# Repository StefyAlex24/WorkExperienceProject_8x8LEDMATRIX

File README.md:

# WorkExperienceProject_8x8LEDMATRIX

Arduino Nano based 8x8 LED matrix board with MAX7219 Controller.
Refer to file: 8x8 LED Matrix.docx for project info.
Also includes Arduino Code files to get you started on your journey.

This project is intended as a work experience assignment for school children of age 14 and over.
The code for this project is based off other open source examples with only minor additions and modifications.

Forking of this project is encouraged.

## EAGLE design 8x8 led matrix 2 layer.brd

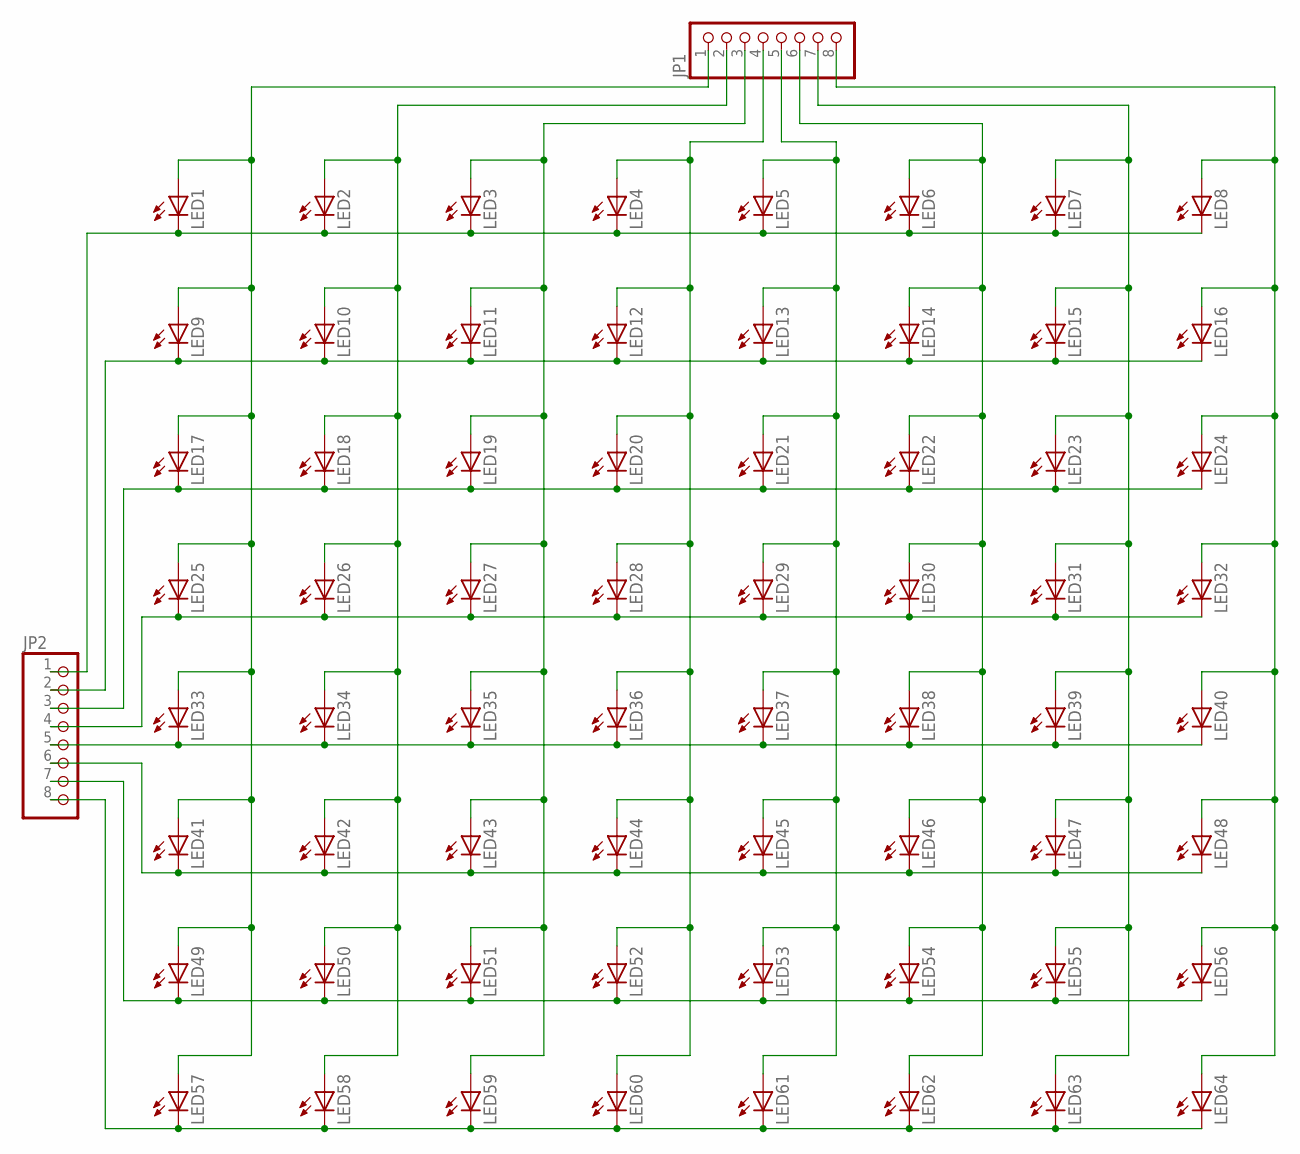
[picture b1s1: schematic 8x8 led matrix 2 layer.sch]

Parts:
JP1, JP2: PINHD-1X8; 1X08
LED1, LED2, LED3, LED4, LED5, LED6, LED7, LED8, LED9, LED10, LED11, LED12, LED13, LED14, LED15, LED16, LED17, LED18, LED19, LED20, LED21, LED22, LED23, LED24, LED25, LED26, LED27, LED28, LED29, LED30, LED31, LED32, LED33, LED34, LED35, LED36, LED37, LED38, LED39, LED40, LED41, LED42, LED43, LED44, LED45, LED46, LED47, LED48, LED49, LED50, LED51, LED52, LED53, LED54, LED55, LED56, LED57, LED58, LED59, LED60, LED61, LED62, LED63, LED64: LED5MM

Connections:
unnamed: JP1.4, LED4.A, LED12.A, LED20.A, LED28.A, LED36.A, LED44.A, LED52.A, LED60.A
unnamed: JP1.5, LED5.A, LED13.A, LED21.A, LED29.A, LED37.A, LED45.A, LED53.A, LED61.A
unnamed: JP1.1, LED1.A, LED9.A, LED17.A
unnamed: JP1.3, LED3.A, LED11.A, LED19.A, LED27.A, LED35.A, LED43.A, LED51.A, LED59.A
unnamed: JP1.6, LED6.A, LED14.A, LED22.A, LED30.A, LED38.A, LED46.A, LED54.A, LED62.A
unnamed: JP1.7, LED7.A, LED15.A, LED23.A, LED31.A, LED39.A, LED47.A, LED55.A, LED63.A
unnamed: JP2.1, LED1.K (C), LED2.K (C), LED3.K (C), LED4.K (C), LED5.K (C), LED6.K (C), LED7.K (C), LED8.K (C)
unnamed: JP2.2, LED9.K (C), LED10.K (C), LED11.K (C), LED12.K (C), LED13.K (C), LED14.K (C), LED15.K (C), LED16.K (C)
unnamed: JP2.3, LED17.K (C), LED18.K (C), LED19.K (C), LED20.K (C), LED21.K (C), LED22.K (C), LED23.K (C), LED24.K (C)
unnamed: LED25.A, LED33.A, LED41.A, LED49.A, LED57.A
unnamed: JP2.4, LED25.K (C), LED26.K (C), LED27.K (C), LED28.K (C), LED29.K (C), LED30.K (C), LED31.K (C), LED32.K (C)
unnamed: JP2.5, LED33.K (C), LED34.K (C), LED35.K (C), LED36.K (C), LED37.K (C), LED38.K (C), LED39.K (C), LED40.K (C)
unnamed: JP2.6, LED41.K (C), LED42.K (C), LED43.K (C), LED44.K (C), LED45.K (C), LED46.K (C), LED47.K (C), LED48.K (C)
unnamed: JP1.8, LED8.A, LED16.A, LED24.A, LED32.A, LED40.A, LED48.A, LED56.A, LED64.A
unnamed: JP2.7, LED49.K (C), LED50.K (C), LED51.K (C), LED52.K (C), LED53.K (C), LED54.K (C), LED55.K (C), LED56.K (C)
unnamed: JP1.2, LED2.A, LED10.A, LED18.A, LED26.A, LED34.A, LED42.A, LED50.A, LED58.A
unnamed: JP2.8, LED57.K (C), LED58.K (C), LED59.K (C), LED60.K (C), LED61.K (C), LED62.K (C), LED63.K (C), LED64.K (C)

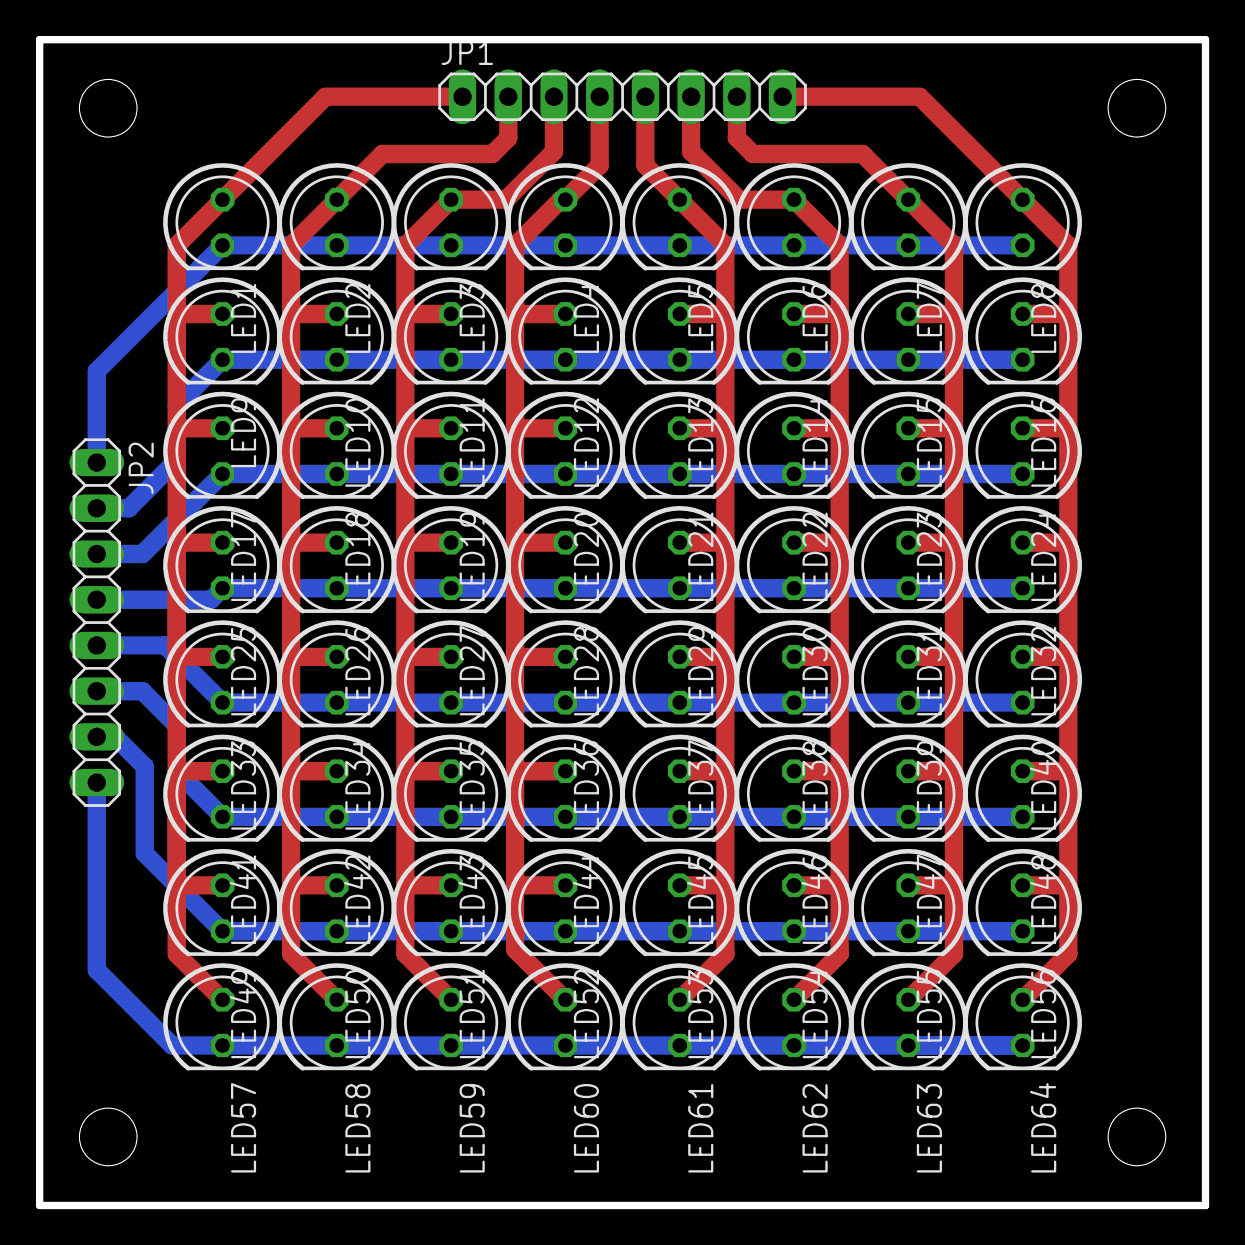
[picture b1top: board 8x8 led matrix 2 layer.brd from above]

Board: 2 copper layers, 64.8 x 64.8 mm, 66 parts (0 on the bottom side), 17 nets.

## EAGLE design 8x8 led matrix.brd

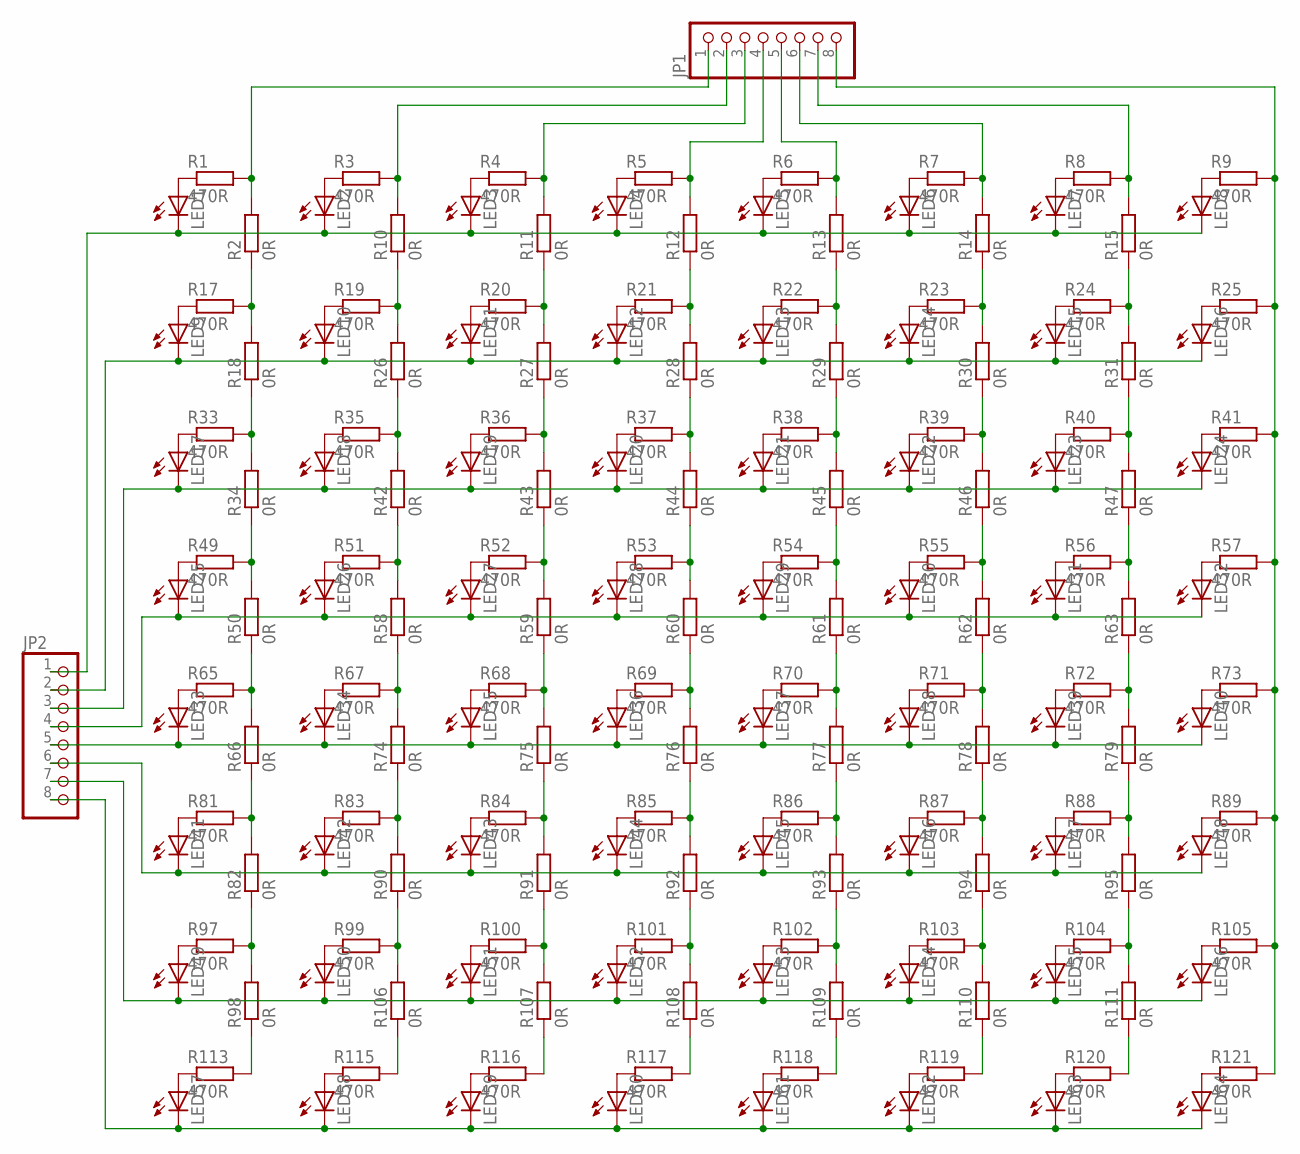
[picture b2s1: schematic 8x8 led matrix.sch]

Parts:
JP1, JP2: PINHD-1X8; 1X08
LED1, LED2, LED3, LED4, LED5, LED6, LED7, LED8, LED9, LED10, LED11, LED12, LED13, LED14, LED15, LED16, LED17, LED18, LED19, LED20, LED21, LED22, LED23, LED24, LED25, LED26, LED27, LED28, LED29, LED30, LED31, LED32, LED33, LED34, LED35, LED36, LED37, LED38, LED39, LED40, LED41, LED42, LED43, LED44, LED45, LED46, LED47, LED48, LED49, LED50, LED51, LED52, LED53, LED54, LED55, LED56, LED57, LED58, LED59, LED60, LED61, LED62, LED63, LED64: LED5MM
R1, R3, R4, R5, R6, R7, R8, R9, R17, R19, R20, R21, R22, R23, R24, R25, R33, R35, R36, R37, R38, R39, R40, R41, R49, R51, R52, R53, R54, R55, R56, R57, R65, R67, R68, R69, R70, R71, R72, R73, R81, R83, R84, R85, R86, R87, R88, R89, R97, R99, R100, R101, R102, R103, R104, R105, R113, R115, R116, R117, R118, R119, R120, R121: 470R; R0603
R2, R10, R11, R12, R13, R14, R15, R18, R26, R27, R28, R29, R30, R31, R34, R42, R43, R44, R45, R46, R47, R50, R58, R59, R60, R61, R62, R63, R66, R74, R75, R76, R77, R78, R79, R82, R90, R91, R92, R93, R94, R95, R98, R106, R107, R108, R109, R110, R111: 0R; R1206

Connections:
unnamed: LED1.A, R1.1
unnamed: LED2.A, R3.1
unnamed: LED3.A, R4.1
unnamed: LED4.A, R5.1
unnamed: LED5.A, R6.1
unnamed: LED6.A, R7.1
unnamed: LED7.A, R8.1
unnamed: LED8.A, R9.1
unnamed: JP1.4, R5.2, R12.2
unnamed: JP1.5, R6.2, R13.2
unnamed: JP1.1, R1.2, R2.2
unnamed: JP1.2, R3.2, R10.2
unnamed: JP1.3, R4.2, R11.2
unnamed: JP1.6, R7.2, R14.2
unnamed: JP1.7, R8.2, R15.2
unnamed: JP2.1, LED1.K (C), LED2.K (C), LED3.K (C), LED4.K (C), LED5.K (C), LED6.K (C), LED7.K (C), LED8.K (C)
unnamed: LED9.A, R17.1
unnamed: LED10.A, R19.1
unnamed: LED11.A, R20.1
unnamed: LED12.A, R21.1
unnamed: LED13.A, R22.1
unnamed: LED14.A, R23.1
unnamed: LED15.A, R24.1
unnamed: LED16.A, R25.1
unnamed: R2.1, R17.2, R18.2
unnamed: R10.1, R19.2, R26.2
unnamed: R11.1, R20.2, R27.2
unnamed: R12.1, R21.2, R28.2
unnamed: R13.1, R22.2, R29.2
unnamed: R14.1, R23.2, R30.2
unnamed: R15.1, R24.2, R31.2
unnamed: JP2.2, LED9.K (C), LED10.K (C), LED11.K (C), LED12.K (C), LED13.K (C), LED14.K (C), LED15.K (C), LED16.K (C)
unnamed: LED17.A, R33.1
unnamed: LED18.A, R35.1
unnamed: LED19.A, R36.1
unnamed: LED20.A, R37.1
unnamed: LED21.A, R38.1
unnamed: LED22.A, R39.1
unnamed: LED23.A, R40.1
unnamed: LED24.A, R41.1
unnamed: R18.1, R33.2, R34.2
unnamed: R26.1, R35.2, R42.2
unnamed: R27.1, R36.2, R43.2
unnamed: R28.1, R37.2, R44.2
unnamed: R29.1, R38.2, R45.2
unnamed: R30.1, R39.2, R46.2
unnamed: R31.1, R40.2, R47.2
unnamed: JP2.3, LED17.K (C), LED18.K (C), LED19.K (C), LED20.K (C), LED21.K (C), LED22.K (C), LED23.K (C), LED24.K (C)
unnamed: LED25.A, R49.1
unnamed: LED26.A, R51.1
unnamed: LED27.A, R52.1
unnamed: LED28.A, R53.1
unnamed: LED29.A, R54.1
unnamed: LED30.A, R55.1
unnamed: LED31.A, R56.1
unnamed: LED32.A, R57.1
unnamed: R34.1, R49.2, R50.2
unnamed: R42.1, R51.2, R58.2
unnamed: R43.1, R52.2, R59.2
unnamed: R44.1, R53.2, R60.2
unnamed: R45.1, R54.2, R61.2
unnamed: R46.1, R55.2, R62.2
unnamed: R47.1, R56.2, R63.2
unnamed: JP2.4, LED25.K (C), LED26.K (C), LED27.K (C), LED28.K (C), LED29.K (C), LED30.K (C), LED31.K (C), LED32.K (C)
unnamed: LED33.A, R65.1
unnamed: LED34.A, R67.1
unnamed: LED35.A, R68.1
unnamed: LED36.A, R69.1
unnamed: LED37.A, R70.1
unnamed: LED38.A, R71.1
unnamed: LED39.A, R72.1
unnamed: LED40.A, R73.1
unnamed: R50.1, R65.2, R66.2
unnamed: R58.1, R67.2, R74.2
unnamed: R59.1, R68.2, R75.2
unnamed: R60.1, R69.2, R76.2
unnamed: R61.1, R70.2, R77.2
unnamed: R62.1, R71.2, R78.2
unnamed: R63.1, R72.2, R79.2
unnamed: JP2.5, LED33.K (C), LED34.K (C), LED35.K (C), LED36.K (C), LED37.K (C), LED38.K (C), LED39.K (C), LED40.K (C)
unnamed: LED41.A, R81.1
unnamed: LED42.A, R83.1
unnamed: LED43.A, R84.1
unnamed: LED44.A, R85.1
unnamed: LED45.A, R86.1
unnamed: LED46.A, R87.1
unnamed: LED47.A, R88.1
unnamed: LED48.A, R89.1
unnamed: R66.1, R81.2, R82.2
unnamed: R74.1, R83.2, R90.2
unnamed: R75.1, R84.2, R91.2
unnamed: R76.1, R85.2, R92.2
unnamed: R77.1, R86.2, R93.2
unnamed: R78.1, R87.2, R94.2
unnamed: R79.1, R88.2, R95.2
unnamed: JP2.6, LED41.K (C), LED42.K (C), LED43.K (C), LED44.K (C), LED45.K (C), LED46.K (C), LED47.K (C), LED48.K (C)
unnamed: LED49.A, R97.1
unnamed: LED50.A, R99.1
unnamed: LED51.A, R100.1
unnamed: LED52.A, R101.1
unnamed: LED53.A, R102.1
unnamed: LED54.A, R103.1
unnamed: LED55.A, R104.1
unnamed: LED56.A, R105.1
unnamed: R82.1, R97.2, R98.2
unnamed: R90.1, R99.2, R106.2
unnamed: R91.1, R100.2, R107.2
unnamed: R92.1, R101.2, R108.2
unnamed: R93.1, R102.2, R109.2
unnamed: R94.1, R103.2, R110.2
unnamed: R95.1, R104.2, R111.2
unnamed: JP1.8, R9.2, R25.2, R41.2, R57.2, R73.2, R89.2, R105.2, R121.2
unnamed: JP2.7, LED49.K (C), LED50.K (C), LED51.K (C), LED52.K (C), LED53.K (C), LED54.K (C), LED55.K (C), LED56.K (C)
unnamed: LED57.A, R113.1
unnamed: LED58.A, R115.1
unnamed: LED59.A, R116.1
unnamed: LED60.A, R117.1
unnamed: LED61.A, R118.1
unnamed: LED62.A, R119.1
unnamed: LED63.A, R120.1
unnamed: LED64.A, R121.1
unnamed: R98.1, R113.2
unnamed: R106.1, R115.2
unnamed: R107.1, R116.2
unnamed: R108.1, R117.2
unnamed: R109.1, R118.2
unnamed: R110.1, R119.2
unnamed: R111.1, R120.2
unnamed: JP2.8, LED57.K (C), LED58.K (C), LED59.K (C), LED60.K (C), LED61.K (C), LED62.K (C), LED63.K (C), LED64.K (C)

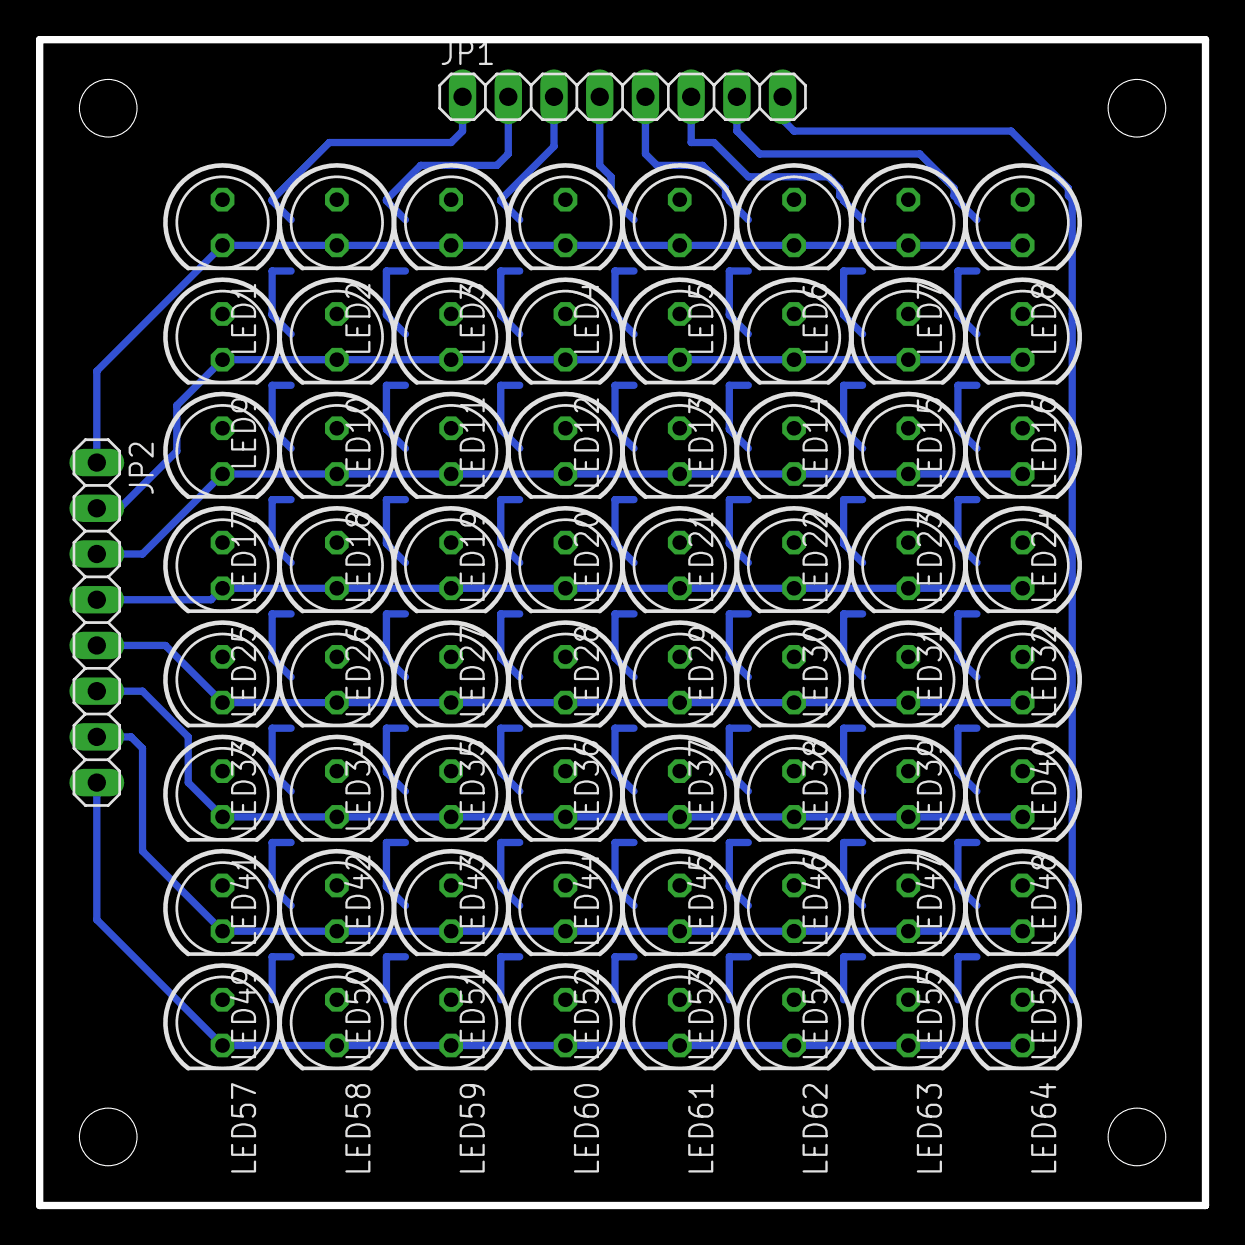
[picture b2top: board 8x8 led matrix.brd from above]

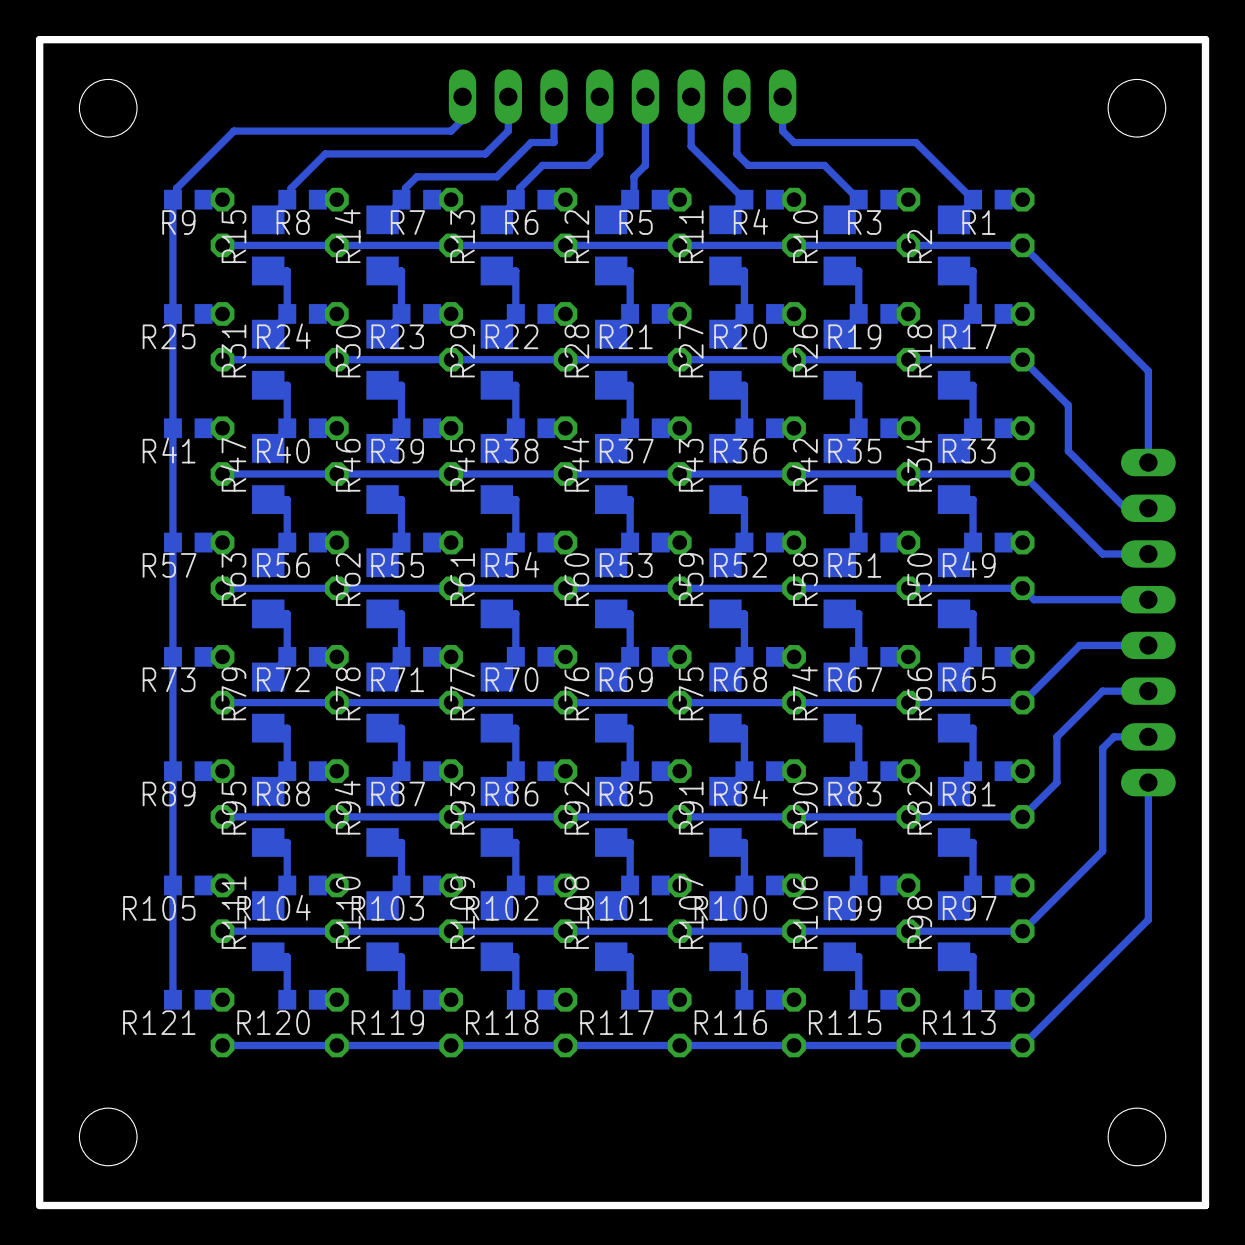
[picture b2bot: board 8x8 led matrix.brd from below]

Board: 2 copper layers, 64.8 x 64.8 mm, 179 parts (113 on the bottom side), 129 nets.

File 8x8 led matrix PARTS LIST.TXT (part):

Partlist

Exported from 8x8 led matrix.brd at 16/08/2016 16:32

EAGLE Version 7.5.0 Copyright (c) 1988-2015 CadSoft

Assembly variant: 

Part     Value          Package  Library  Position (mm)         Orientation

JP1                     1X08     pinhead  (46.355 73.025)       R0
JP2                     1X08     pinhead  (17.145 43.815)       R270
LED1                    LED5MM   led      (24.13 66.04)         R270
LED2                    LED5MM   led      (30.48 66.04)         R270
LED3                    LED5MM   led      (36.83 66.04)         R270
LED4                    LED5MM   led      (43.18 66.04)         R270
LED5                    LED5MM   led      (49.53 66.04)         R270
LED6                    LED5MM   led      (55.88 66.04)         R270
LED7                    LED5MM   led      (62.23 66.04)         R270
LED8                    LED5MM   led      (68.58 66.04)         R270
LED9                    LED5MM   led      (24.13 59.69)         R270
LED10                   LED5MM   led      (30.48 59.69)         R270
LED11                   LED5MM   led      (36.83 59.69)         R270
LED12                   LED5MM   led      (43.18 59.69)         R270
LED13                   LED5MM   led      (49.53 59.69)         R270
LED14                   LED5MM   led      (55.88 59.69)         R270
LED15                   LED5MM   led      (62.23 59.69)         R270
LED16                   LED5MM   led      (68.58 59.69)         R270
LED17                   LED5MM   led      (24.13 53.34)         R270
LED18                   LED5MM   led      (30.48 53.34)         R270
LED19                   LED5MM   led      (36.83 53.34)         R270
LED20                   LED5MM   led      (43.18 53.34)         R270
LED21                   LED5MM   led      (49.53 53.34)         R270
LED22                   LED5MM   led      (55.88 53.34)         R270
LED23                   LED5MM   led      (62.23 53.34)         R270
LED24                   LED5MM   led      (68.58 53.34)         R270
LED25                   LED5MM   led      (24.13 46.99)         R270
LED26                   LED5MM   led      (30.48 46.99)         R270
LED27                   LED5MM   led      (36.83 46.99)         R270
LED28                   LED5MM   led      (43.18 46.99)         R270
LED29                   LED5MM   led      (49.53 46.99)         R270
LED30                   LED5MM   led      (55.88 46.99)         R270
LED31                   LED5MM   led      (62.23 46.99)         R270
LED32                   LED5MM   led      (68.58 46.99)         R270
LED33                   LED5MM   led      (24.13 40.64)         R270
LED34                   LED5MM   led      (30.48 40.64)         R270
LED35                   LED5MM   led      (36.83 40.64)         R270
LED36                   LED5MM   led      (43.18 40.64)         R270
LED37                   LED5MM   led      (49.53 40.64)         R270
LED38                   LED5MM   led      (55.88 40.64)         R270
LED39                   LED5MM   led      (62.23 40.64)         R270
LED40                   LED5MM   led      (68.58 40.64)         R270
LED41                   LED5MM   led      (24.13 34.29)         R270
LED42                   LED5MM   led      (30.48 34.29)         R270
LED43                   LED5MM   led      (36.83 34.29)         R270
LED44                   LED5MM   led      (43.18 34.29)         R270
LED45                   LED5MM   led      (49.53 34.29)         R270
LED46                   LED5MM   led      (55.88 34.29)         R270
LED47                   LED5MM   led      (62.23 34.29)         R270
LED48                   LED5MM   led      (68.58 34.29)         R270
LED49                   LED5MM   led      (24.13 27.94)         R270
LED50                   LED5MM   led      (30.48 27.94)         R270
LED51                   LED5MM   led      (36.83 27.94)         R270
LED52                   LED5MM   led      (43.18 27.94)         R270
LED53                   LED5MM   led      (49.53 27.94)         R270
LED54                   LED5MM   led      (55.88 27.94)         R270
LED55                   LED5MM   led      (62.23 27.94)         R270
LED56                   LED5MM   led      (68.58 27.94)         R270
LED57                   LED5MM   led      (24.13 21.59)         R270
LED58                   LED5MM   led      (30.48 21.59)         R270
LED59                   LED5MM   led      (36.83 21.59)         R270
LED60                   LED5MM   led      (43.18 21.59)         R270
LED61                   LED5MM   led      (49.53 21.59)         R270
LED62                   LED5MM   led      (55.88 21.59)         R270
LED63                   LED5MM   led      (62.23 21.59)         R270
LED64                   LED5MM   led      (68.58 21.59)         R270
R1       470R           R0603    resistor (26.035 67.31)        MR180
R2       0R             R1206    resistor (27.94 64.77)         MR90
R3       470R           R0603    resistor (32.385 67.31)        MR180
R4       470R           R0603    resistor (38.735 67.31)        MR180
R5       470R           R0603    resistor (45.085 67.31)        MR180
R6       470R           R0603    resistor (51.435 67.31)        MR180
R7       470R           R0603    resistor (57.785 67.31)        MR180
R8       470R           R0603    resistor (64.135 67.31)        MR180
R9       470R           R0603    resistor (70.485 67.31)        MR180
R10      0R             R1206    resistor (34.29 64.77)         MR90
R11      0R             R1206    resistor (40.64 64.77)         MR90
R12      0R             R1206    resistor (46.99 64.77)         MR90
R13      0R             R1206    resistor (53.34 64.77)         MR90
R14      0R             R1206    resistor (59.69 64.77)         MR90
R15      0R             R1206    resistor (66.04 64.77)         MR90
R17      470R           R0603    resistor (26.035 60.96)        MR180
R18      0R             R1206    resistor (27.94 58.42)         MR90
R19      470R           R0603    resistor (32.385 60.96)        MR180
R20      470R           R0603    resistor (38.735 60.96)        MR180
R21      470R           R0603    resistor (45.085 60.96)        MR180
R22      470R           R0603    resistor (51.435 60.96)        MR180
R23      470R           R0603    resistor (57.785 60.96)        MR180
R24      470R           R0603    resistor (64.135 60.96)        MR180
R25      470R           R0603    resistor (70.485 60.96)        MR180
R26      0R             R1206    resistor (34.29 58.42)         MR90
R27      0R             R1206    resistor (40.64 58.42)         MR90
R28      0R             R1206    resistor (46.99 58.42)         MR90
R29      0R             R1206    resistor (53.34 58.42)         MR90
R30      0R             R1206    resistor (59.69 58.42)         MR90
R31      0R             R1206    resistor (66.04 58.42)         MR90
R33      470R           R0603    resistor (26.035 54.61)        MR180
R34      0R             R1206    resistor (27.94 52.07)         MR90
R35      470R           R0603    resistor (32.385 54.61)        MR180
R36      470R           R0603    resistor (38.735 54.61)        MR180
R37      470R           R0603    resistor (45.085 54.61)        MR180
R38      470R           R0603    resistor (51.435 54.61)        MR180
R39      470R           R0603    resistor (57.785 54.61)        MR180
R40      470R           R0603    resistor (64.135 54.61)        MR180
R41      470R           R0603    resistor (70.485 54.61)        MR180
R42      0R             R1206    resistor (34.29 52.07)         MR90
R43      0R             R1206    resistor (40.64 52.07)         MR90
R44      0R             R1206    resistor (46.99 52.07)         MR90
R45      0R             R1206    resistor (53.34 52.07)         MR90
R46      0R             R1206    resistor (59.69 52.07)         MR90
R47      0R             R1206    resistor (66.04 52.07)         MR90
R49      470R           R0603    resistor (26.035 48.26)        MR180
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
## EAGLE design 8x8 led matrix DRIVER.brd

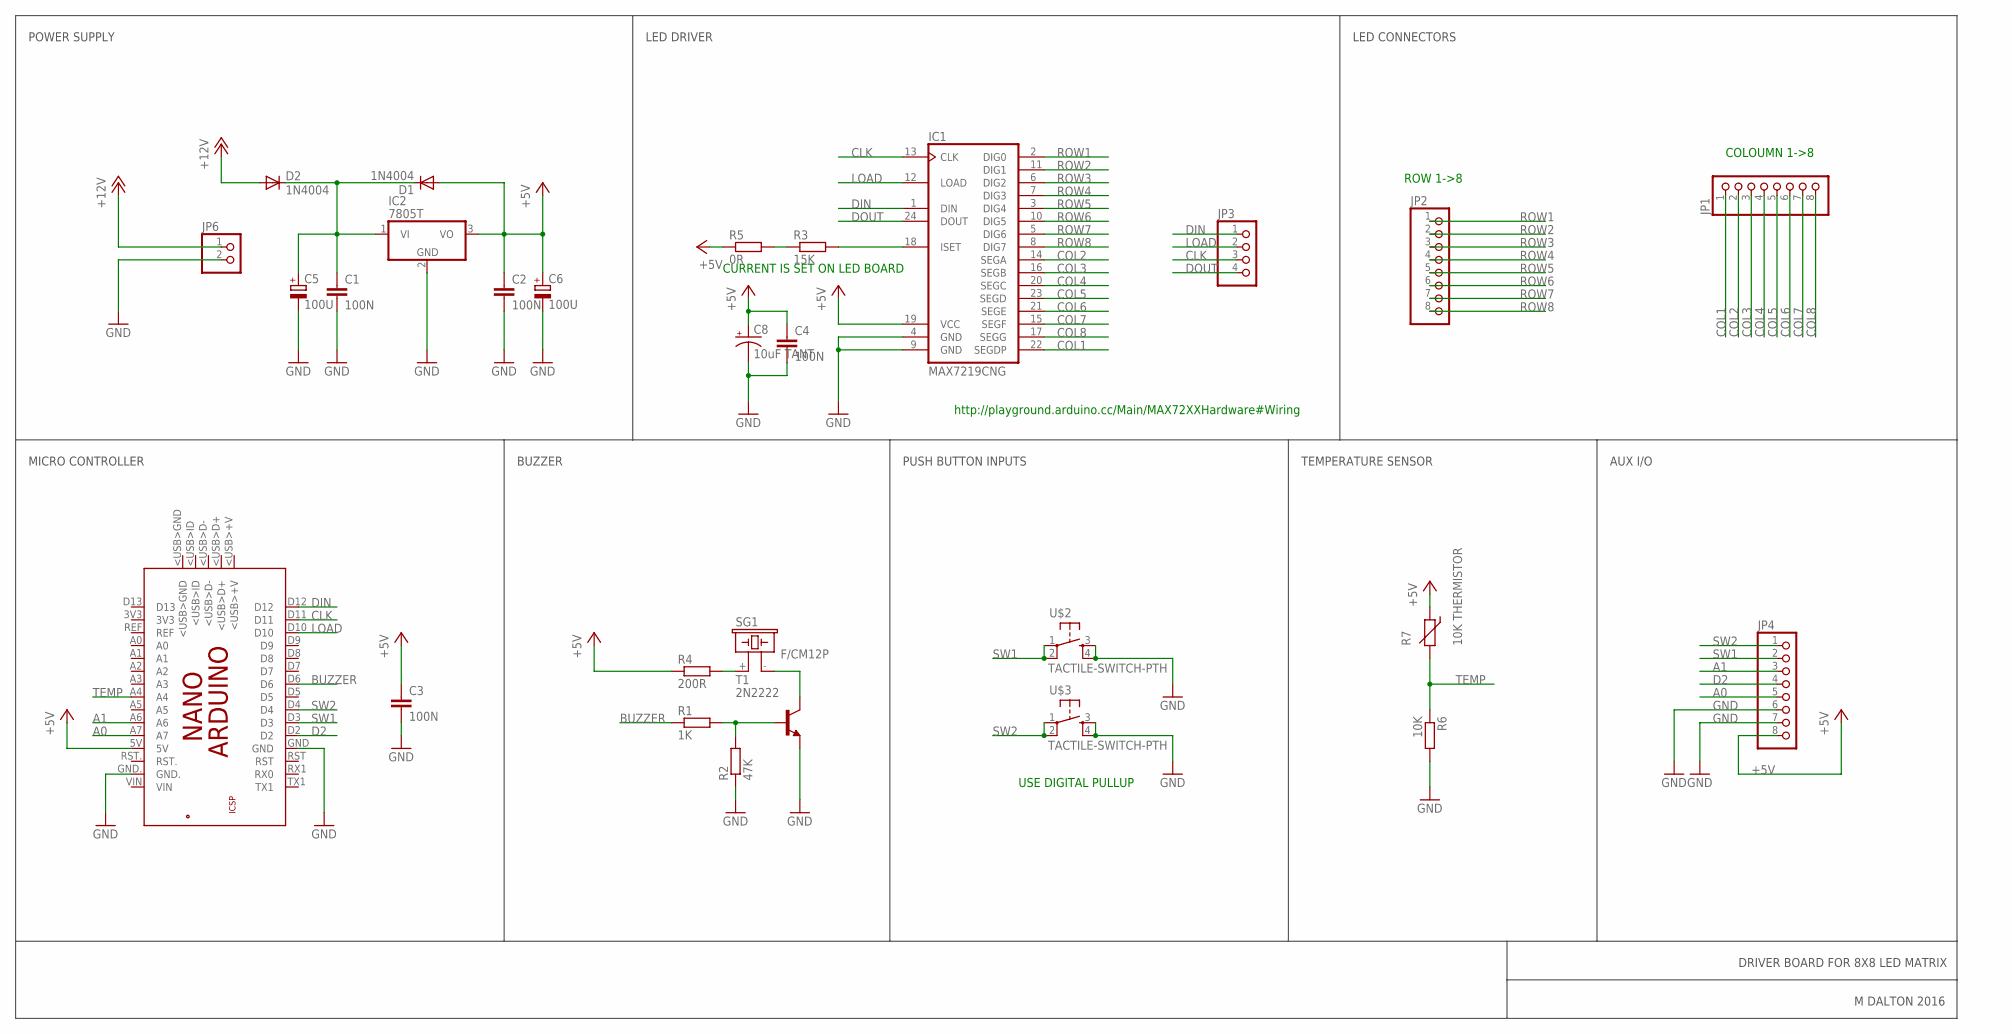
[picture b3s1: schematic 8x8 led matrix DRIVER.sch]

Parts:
C1, C2, C3, C4: 100N; C1206K
C5, C6: 100U; E5-10,5
C8: 10uF TANT; EIA3216
D1, D2: 1N4004; DO41-10
IC1: MAX7219CNG; DIL24-3
IC2: 7805T; TO220H
JP1, JP2, JP4: PINHD-1X8; 1X08
JP3: PINHD-1X4; 1X04
JP6: PINHD-1X2; 1X02
PCB1: ARDUINO_NANO
R1: 1K; M1206
R2: 47K; M1206
R3: 15K; M0805
R4: 200R; M1206
R5: 0R; M0805
R6: 10K; M1206
R7: 10K THERMISTOR; R-7,5
SG1: F/CM12P
T1: 2N2222; TO92-EBC-OVAL
U$2, U$3: TACTILE-SWITCH-PTH; TAC-SWITCH-PTH

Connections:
+5V: C2.1, C3.1, C4.1, C6.+, C8.A (+), D1.A, IC1.19 (VCC), IC2.3 (VO), JP4.8, PCB1.5V, R4.1, R5.1, R7.1
+12V: D2.A, JP6.1
A0: JP4.5, PCB1.A7
A1: JP4.3, PCB1.A6
BUZZER: PCB1.D6, R1.1
CLK: IC1.13 (CLK), JP3.3, PCB1.D11
COL1: IC1.22 (SEGDP), JP1.1
COL2: IC1.14 (SEGA), JP1.2
COL3: IC1.16 (SEGB), JP1.3
COL4: IC1.20 (SEGC), JP1.4
COL5: IC1.23 (SEGD), JP1.5
COL6: IC1.21 (SEGE), JP1.6
COL7: IC1.15 (SEGF), JP1.7
COL8: IC1.17 (SEGG), JP1.8
D2: JP4.4, PCB1.D2
DIN: IC1.1 (DIN), JP3.1, PCB1.D12
DOUT: IC1.24 (DOUT), JP3.4
GND: C1.2, C2.2, C3.2, C4.2, C5.-, C6.-, C8.C (-), IC1.4 (GND), IC1.9 (GND), IC2.2 (GND), JP4.6, JP4.7, JP6.2, PCB1.GND, PCB1.GND., R2.1, R6.2, T1.E, U$2.3, U$2.4, U$3.3, U$3.4
LOAD: IC1.12 (LOAD), JP3.2, PCB1.D10
unnamed: R3.1, R5.2
unnamed: C1.1, C5.+, D1.C, D2.C, IC2.1 (VI)
unnamed: IC1.18 (ISET), R3.2
unnamed: R1.2, R2.2, T1.B
unnamed: SG1.- (2), T1.C
unnamed: R4.2, SG1.+ (1)
ROW1: IC1.2 (DIG0), JP2.1
ROW2: IC1.11 (DIG1), JP2.2
ROW3: IC1.6 (DIG2), JP2.3
ROW4: IC1.7 (DIG3), JP2.4
ROW5: IC1.3 (DIG4), JP2.5
ROW6: IC1.10 (DIG5), JP2.6
ROW7: IC1.5 (DIG6), JP2.7
ROW8: IC1.8 (DIG7), JP2.8
SW1: JP4.2, PCB1.D3, U$2.1, U$2.2
SW2: JP4.1, PCB1.D4, U$3.1, U$3.2
TEMP: PCB1.A4, R6.1, R7.2

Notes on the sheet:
ROW 1->8
COLOUMN 1->8
http://playground.arduino.cc/Main/MAX72XXHardware#Wiring
CURRENT IS SET ON LED BOARD
USE DIGITAL PULLUP
POWER SUPPLY
LED DRIVER
LED CONNECTORS
MICRO CONTROLLER
BUZZER
PUSH BUTTON INPUTS
TEMPERATURE SENSOR
AUX I/O
DRIVER BOARD FOR 8X8 LED MATRIX
M DALTON 2016

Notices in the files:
parts and their libraries:
GeekAmmo: Licensing:Creative Commons ShareAlike 4.0 International - https://creativecommons.org/licenses/by-sa/4.0
